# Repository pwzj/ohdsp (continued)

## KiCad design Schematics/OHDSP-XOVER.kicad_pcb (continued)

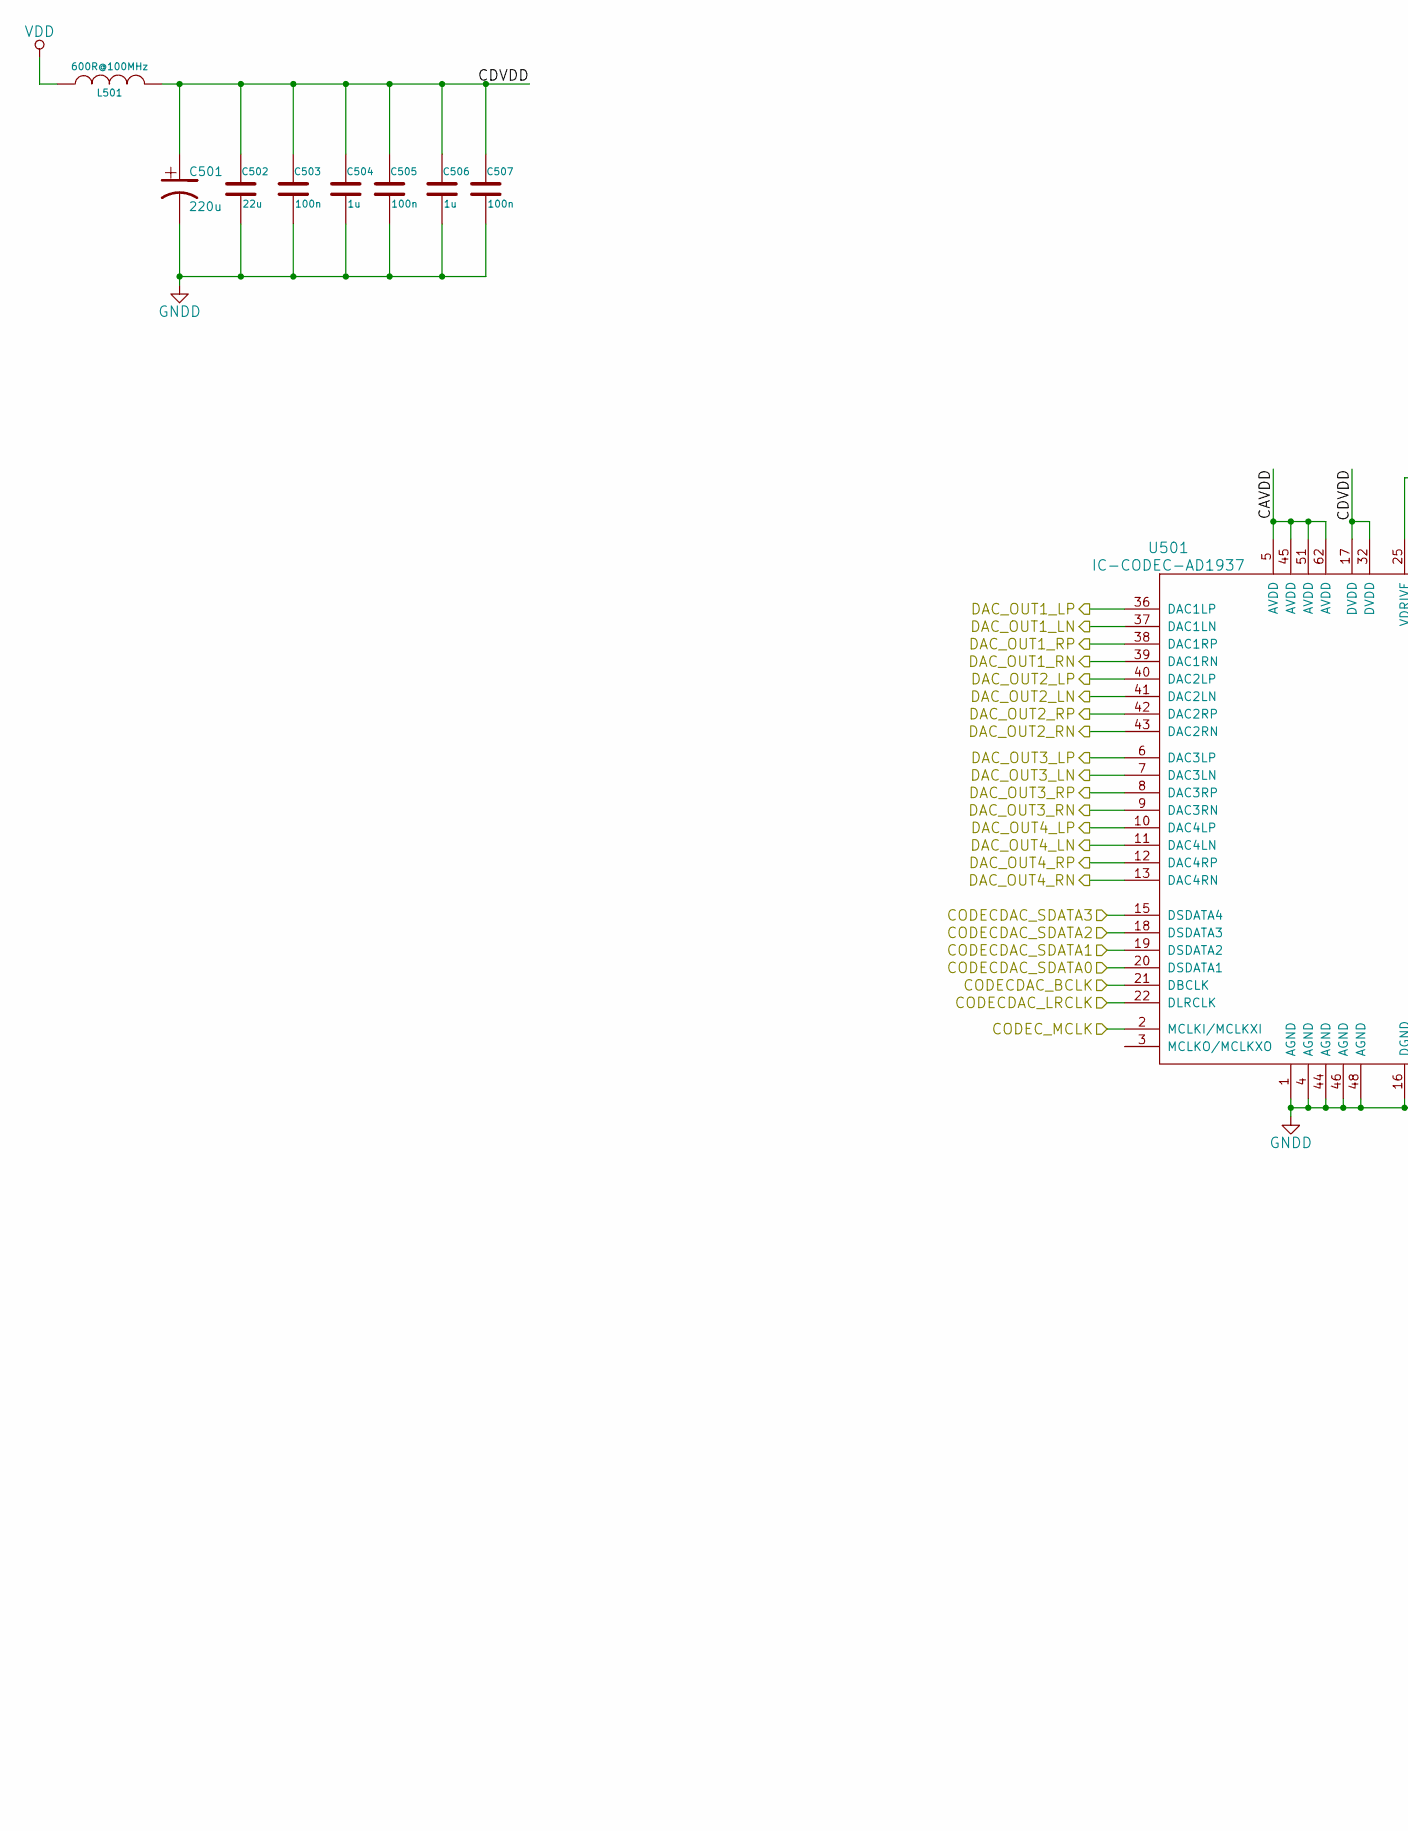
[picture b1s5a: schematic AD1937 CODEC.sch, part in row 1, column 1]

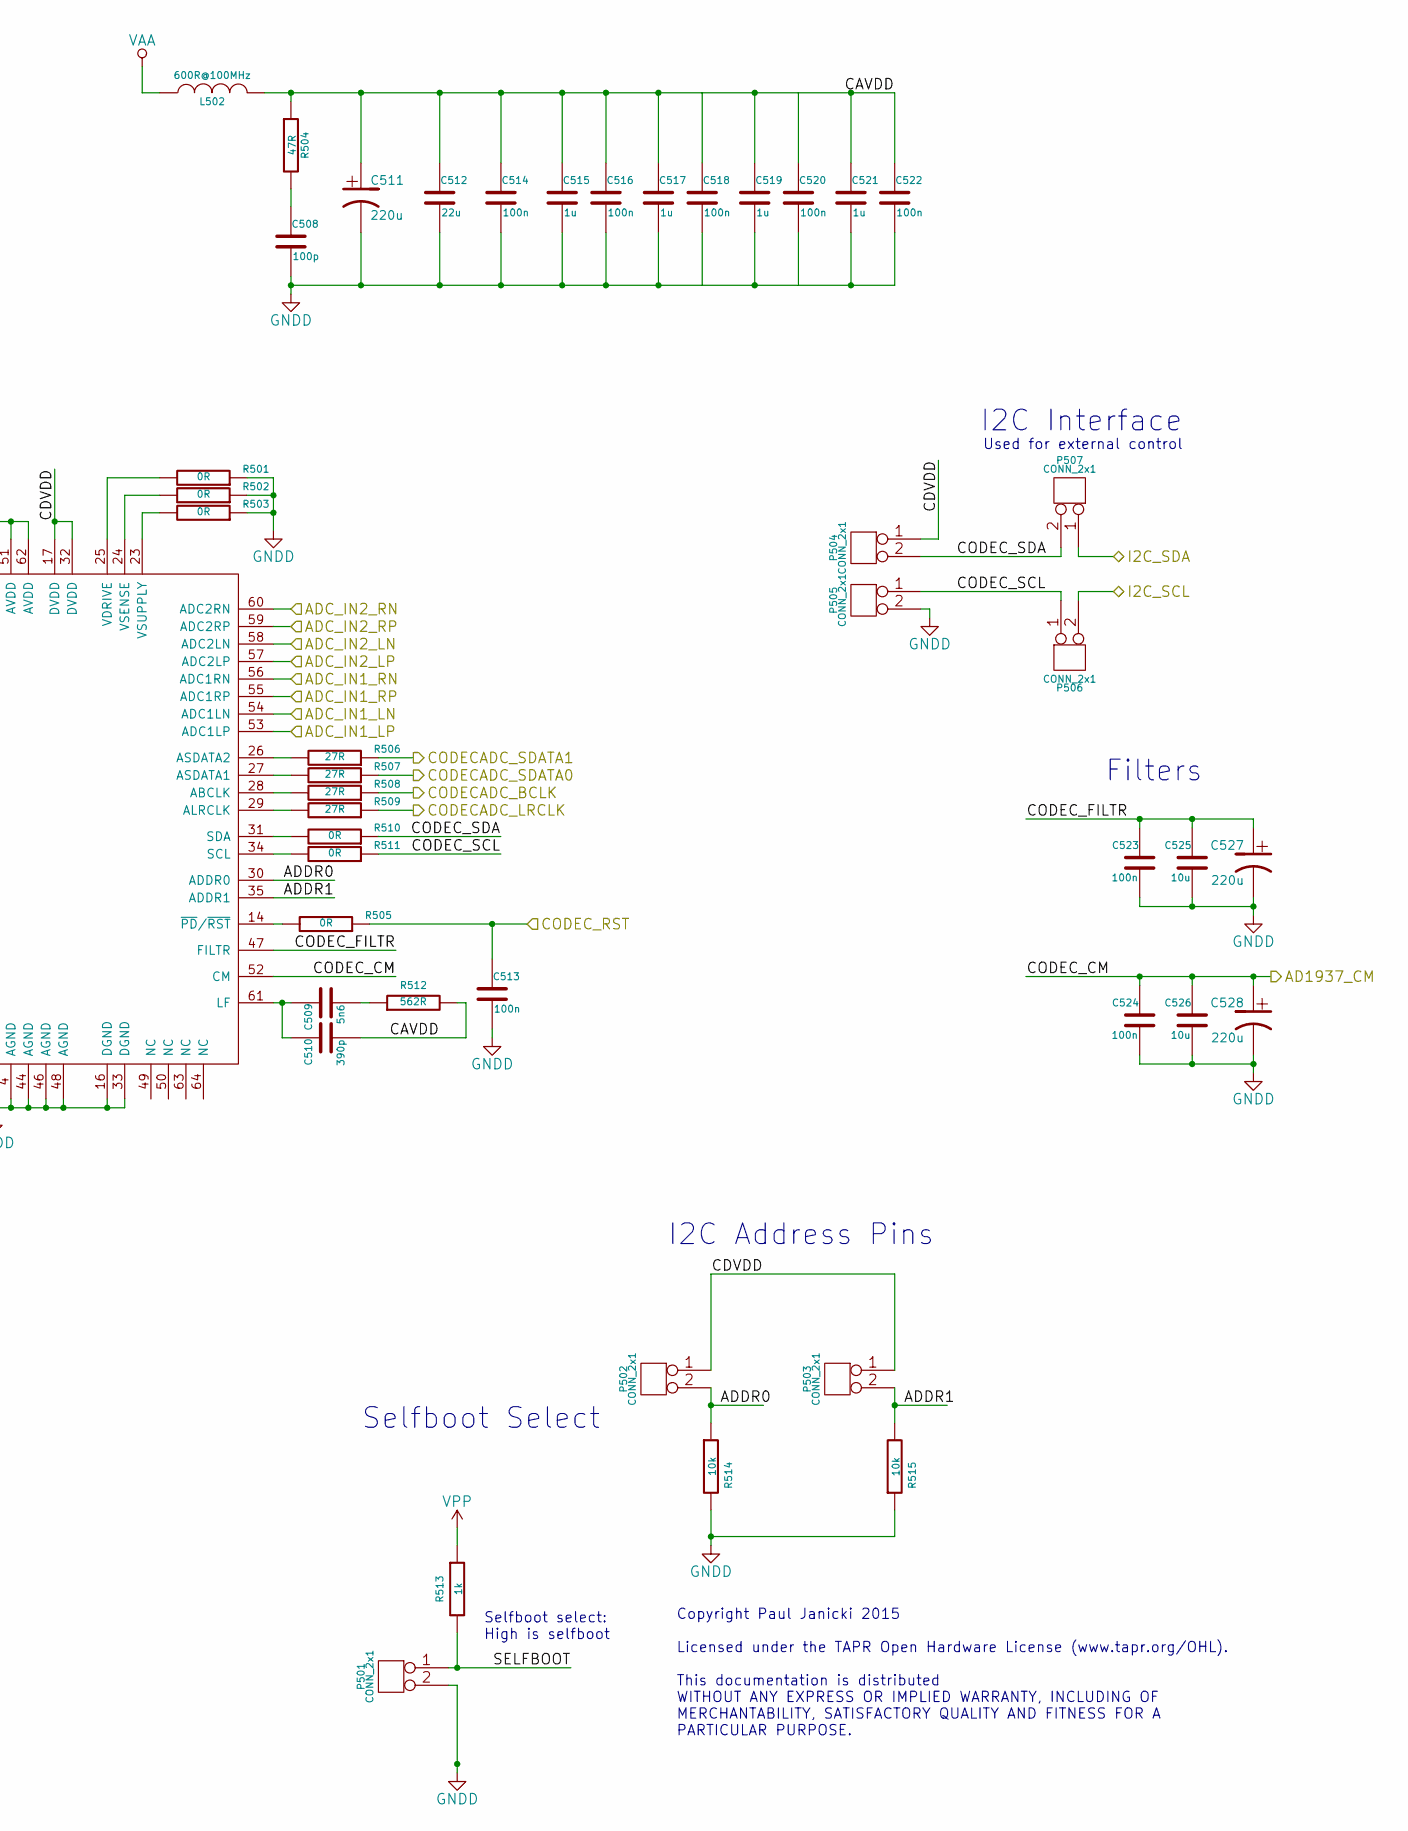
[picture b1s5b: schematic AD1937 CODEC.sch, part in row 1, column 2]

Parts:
C501, C527, C528: 220u; CAP-TH-D6.3mmP2.5mm
C502, C512: 22u; SMD-0805
C503, C505, C507, C513, C514, C516, C518, C520, C522, C523, C524: 100n; SMD-0805
C504, C506, C515, C517, C519, C521: 1u; SMD-0805
C508: 100p; SMD-0805
C509: 5n6; SMD-0805
C510: 390p; SMD-0805
C511: 220u; CAP-TH-D8mmP3.5mm
C525, C526: 10u; SMD-0805
L501, L502: 600R@100MHz; SMD-0805
P501, P502, P503, P504, P505, P506, P507: CONN_2x1; CONN_SIL_2
R501, R502, R503, R505, R510, R511: 0R; SMD-0805
R504: 47R; SMD-0805
R506, R507, R508, R509: 27R; SMD-0805
R512: 562R; SMD-0805
R513: 1k; SMD-0805
R514, R515: 10k; SMD-0805
U501: IC-CODEC-AD1937; IC-LQFP64

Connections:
/AD1937 CODEC/AD1937_CM: C524.1, C526.1, C528.1, U501.52 (CM); also elsewhere on the board
/AD1937 CODEC/ADDR0: P502.2, R514.1, U501.30 (ADDR0)
/AD1937 CODEC/ADDR1: P503.2, R515.2, U501.35 (ADDR1)
/AD1937 CODEC/CAVDD: C510.2, C511.1, C512.1, C514.1, C515.1, C516.1, C517.1, C519.1, C521.1, C522.1, L502.2, R504.1, R512.2, U501.5 (AVDD), U501.45 (AVDD), U501.51 (AVDD), U501.62 (AVDD)
/AD1937 CODEC/CDVDD: C501.1, C502.1, C503.1, C504.1, C505.1, C506.1, C507.1, L501.2, P502.1, P503.1, P504.1, U501.17 (DVDD), U501.32 (DVDD)
/AD1937 CODEC/CODECDAC_BCLK: U501.21 (DBCLK); also elsewhere on the board
/AD1937 CODEC/CODECDAC_LRCLK: U501.22 (DLRCLK); also elsewhere on the board
/AD1937 CODEC/CODECDAC_SDATA0: U501.20 (DSDATA1); also elsewhere on the board
/AD1937 CODEC/CODECDAC_SDATA1: U501.19 (DSDATA2); also elsewhere on the board
/AD1937 CODEC/CODECDAC_SDATA2: U501.18 (DSDATA3); also elsewhere on the board
/AD1937 CODEC/CODECDAC_SDATA3: U501.15 (DSDATA4); also elsewhere on the board
/AD1937 CODEC/CODEC_FILTR: C523.1, C525.1, C527.1, U501.47 (FILTR)
/AD1937 CODEC/CODEC_MCLK: U501.2 (MCLKI/MCLKXI); also elsewhere on the board
/AD1937 CODEC/CODEC_RST: C513.1, R505.1; also elsewhere on the board
/AD1937 CODEC/CODEC_SCL: P505.1, P506.1, R511.1
/AD1937 CODEC/CODEC_SDA: P504.2, P507.2, R510.1
/AD1937 CODEC/DAC_OUT1_LN: U501.37 (DAC1LN); also elsewhere on the board
/AD1937 CODEC/DAC_OUT1_LP: U501.36 (DAC1LP); also elsewhere on the board
/AD1937 CODEC/DAC_OUT1_RN: U501.39 (DAC1RN); also elsewhere on the board
/AD1937 CODEC/DAC_OUT1_RP: U501.38 (DAC1RP); also elsewhere on the board
/AD1937 CODEC/DAC_OUT2_LN: U501.41 (DAC2LN); also elsewhere on the board
/AD1937 CODEC/DAC_OUT2_LP: U501.40 (DAC2LP); also elsewhere on the board
/AD1937 CODEC/DAC_OUT2_RN: U501.43 (DAC2RN); also elsewhere on the board
/AD1937 CODEC/DAC_OUT2_RP: U501.42 (DAC2RP); also elsewhere on the board
/AD1937 CODEC/DAC_OUT3_LN: U501.7 (DAC3LN); also elsewhere on the board
/AD1937 CODEC/DAC_OUT3_LP: U501.6 (DAC3LP); also elsewhere on the board
/AD1937 CODEC/DAC_OUT3_RN: U501.9 (DAC3RN); also elsewhere on the board
/AD1937 CODEC/DAC_OUT3_RP: U501.8 (DAC3RP); also elsewhere on the board
/AD1937 CODEC/DAC_OUT4_LN: U501.11 (DAC4LN); also elsewhere on the board
/AD1937 CODEC/DAC_OUT4_LP: U501.10 (DAC4LP); also elsewhere on the board
/AD1937 CODEC/DAC_OUT4_RN: U501.13 (DAC4RN); also elsewhere on the board
/AD1937 CODEC/DAC_OUT4_RP: U501.12 (DAC4RP); also elsewhere on the board
/AD1937 CODEC/I2C_SCL: P506.2; also elsewhere on the board
/AD1937 CODEC/I2C_SDA: P507.1; also elsewhere on the board
/AD1937 CODEC/SELFBOOT: P501.1, R513.2
/AD1937_AnaIn/AD1937_ANAIN_1N: U501.54 (ADC1LN); also elsewhere on the board
/AD1937_AnaIn/AD1937_ANAIN_1P: U501.53 (ADC1LP); also elsewhere on the board
/AD1937_AnaIn/AD1937_ANAIN_2N: U501.56 (ADC1RN); also elsewhere on the board
/AD1937_AnaIn/AD1937_ANAIN_2P: U501.55 (ADC1RP); also elsewhere on the board
/AD1937_AnaIn/AD1937_ANAIN_3N: U501.58 (ADC2LN); also elsewhere on the board
/AD1937_AnaIn/AD1937_ANAIN_3P: U501.57 (ADC2LP); also elsewhere on the board
/AD1937_AnaIn/AD1937_ANAIN_4N: U501.60 (ADC2RN); also elsewhere on the board
/AD1937_AnaIn/AD1937_ANAIN_4P: U501.59 (ADC2RP); also elsewhere on the board
/ADAU1701/ADCIN_BCLK0: R508.1; also elsewhere on the board
/ADAU1701/ADCIN_LRCLK0: R509.1; also elsewhere on the board
/ADAU1701/ADCIN_SDATA0: R507.1; also elsewhere on the board
/ADAU1701/ADCIN_SDATA1: R506.1; also elsewhere on the board
GNDD: C501.2, C502.2, C503.2, C504.2, C505.2, C506.2, C507.2, C508.2, C511.2, C512.2, C513.2, C514.2, C515.2, C516.2, C517.2, C519.2, C521.2, C522.2, C523.2, C524.2, C525.2, C526.2, C527.2, C528.2, P501.2, P505.2, R501.1, R502.1, R503.1, R514.2, R515.1, U501.1 (AGND), U501.4 (AGND), U501.16 (DGND), U501.33 (DGND), U501.44 (AGND), U501.46 (AGND), U501.48 (AGND); also elsewhere on the board
unnamed: C508.1, R504.2
unnamed: C509.1, C510.1, U501.61 (LF)
unnamed: C509.2, R512.1
unnamed: R501.2, U501.25 (VDRIVE)
unnamed: R502.2, U501.24 (VSENSE)
unnamed: R503.2, U501.23 (VSUPPLY)
unnamed: R505.2, U501.14 (~PD~/~RST)
unnamed: R506.2, U501.26 (ASDATA2)
unnamed: R507.2, U501.27 (ASDATA1)
unnamed: R508.2, U501.28 (ABCLK)
unnamed: R509.2, U501.29 (ALRCLK)
unnamed: R510.2, U501.31 (SDA)
unnamed: R511.2, U501.34 (SCL)
VAA: L502.1; also elsewhere on the board
VDD: L501.1; also elsewhere on the board
VPP: R513.1; also elsewhere on the board

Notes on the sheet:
Selfboot Select
Selfboot select: High is selfboot
I2C Interface
Used for external control
Copyright Paul Janicki 2015 Licensed under the TAPR Open Hardware License (www.tapr.org/OHL). This documentation is distributed WITHOUT ANY EXPRESS OR IMPLIED WARRANTY, INCLUDING OF MERCHANTABILITY, SATISFACTORY QUALITY AND FITNESS FOR A PARTICULAR PURPOSE.
I2C Address Pins
Filters

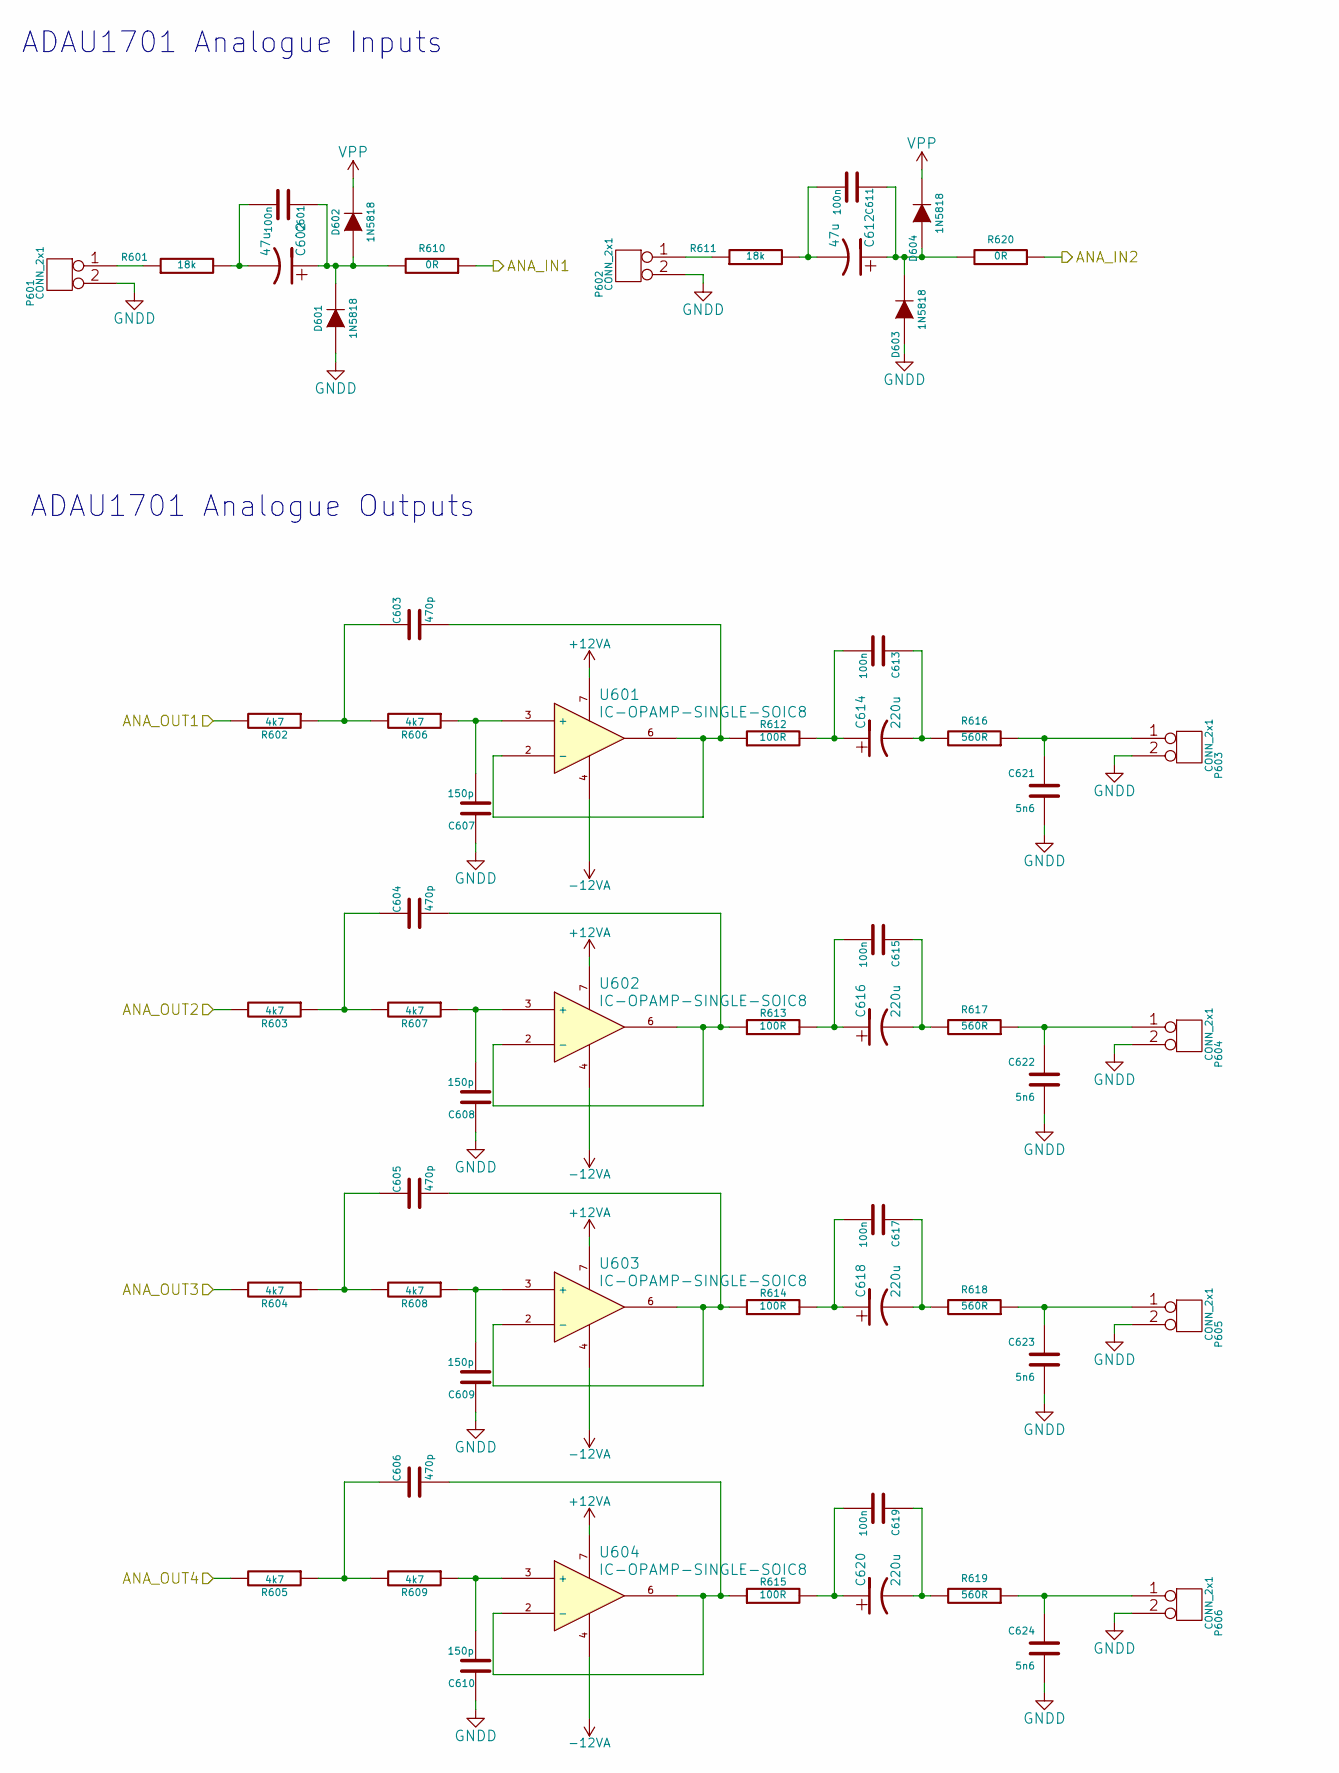
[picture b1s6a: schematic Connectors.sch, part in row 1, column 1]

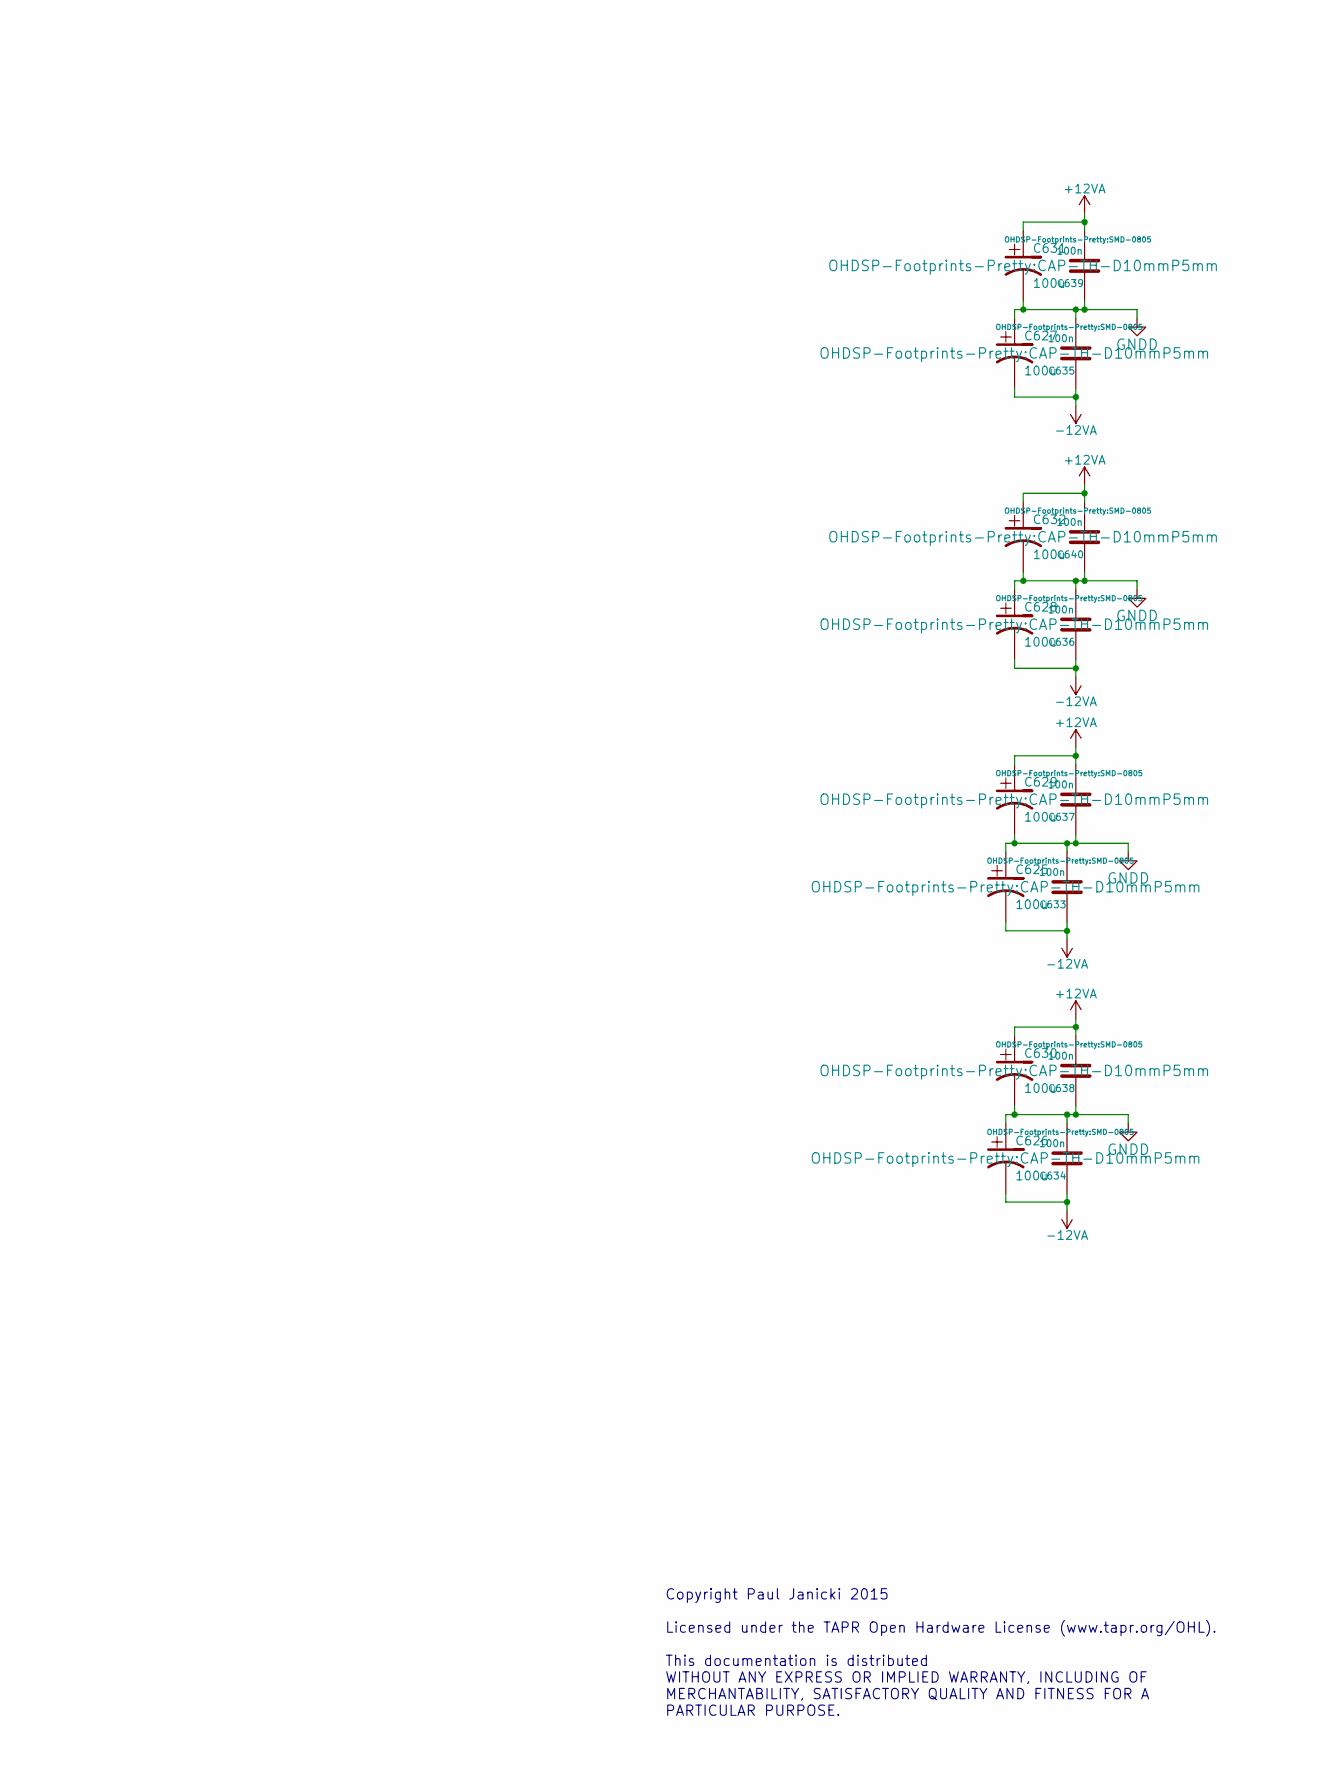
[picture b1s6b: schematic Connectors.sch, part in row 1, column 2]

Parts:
C601, C611, C613, C615, C617, C619: 100n; CAP_TH_5mm
C602, C612: 47u; CAP-TH-D10mmP5mm
C603, C604, C605, C606: 470p; CAP_TH_5mm
C607, C608, C609, C610: 150p; CAP_TH_5mm
C614, C616, C618, C620: 220u; CAP-TH-D10mmP5mm
C621, C622, C623, C624: 5n6; CAP_TH_5mm
C625, C626, C627, C628, C629, C630, C631, C632: 100u; CAP-TH-D10mmP5mm
C633, C634, C635, C636, C637, C638, C639, C640: 100n; SMD-0805
D601, D602, D603, D604: 1N5818; DIODE-DO-41
P601, P602, P603, P604, P605, P606: CONN_2x1; CONN_SIL_2
R601, R611: 18k; TH-RES-0W25
R602, R603, R604, R605, R606, R607, R608, R609: 4k7; TH-RES-0W25
R610, R620: 0R; TH-RES-0W25
R612, R613, R614, R615: 100R; TH-RES-0W25
R616, R617, R618, R619: 560R; TH-RES-0W25
U601, U602, U603, U604: IC-OPAMP-SINGLE-SOIC8; IC_DIP_8

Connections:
+12VA: C629.1, C630.1, C631.1, C632.1, C637.2, C638.2, C639.2, C640.2, U601.7, U602.7, U603.7, U604.7; also elsewhere on the board
-12VA: C625.2, C626.2, C627.2, C628.2, C633.1, C634.1, C635.1, C636.1, U601.4, U602.4, U603.4, U604.4; also elsewhere on the board
/ADAU1701/ADC_IN0: R610.1; also elsewhere on the board
/ADAU1701/ADC_IN1: R620.1; also elsewhere on the board
/Connectors/ANA_OUT1: R602.2; also elsewhere on the board
/Connectors/ANA_OUT2: R603.2; also elsewhere on the board
/Connectors/ANA_OUT3: R604.2; also elsewhere on the board
/Connectors/ANA_OUT4: R605.2; also elsewhere on the board
GNDD: C607.1, C608.1, C609.1, C610.1, C621.2, C622.2, C623.2, C624.2, C625.1, C626.1, C627.1, C628.1, C629.2, C630.2, C631.2, C632.2, C633.2, C634.2, C635.2, C636.2, C637.1, C638.1, C639.1, C640.1, D601.1 (A), D603.1 (A), P601.2, P602.2, P603.2, P604.2, P605.2, P606.2; also elsewhere on the board
unnamed: C601.1, C602.1, D601.2 (K), D602.1 (A), R610.2
unnamed: C601.2, C602.2, R601.2
unnamed: C603.1, R602.1, R606.2
unnamed: C603.2, R612.1, U601.2 (-), U601.6
unnamed: C604.1, R603.1, R607.2
unnamed: C604.2, R613.1, U602.2 (-), U602.6
unnamed: C605.1, R604.1, R608.2
unnamed: C605.2, R614.1, U603.2 (-), U603.6
unnamed: C606.1, R605.1, R609.2
unnamed: C606.2, R615.1, U604.2 (-), U604.6
unnamed: C607.2, R606.1, U601.3 (+)
unnamed: C608.2, R607.1, U602.3 (+)
unnamed: C609.2, R608.1, U603.3 (+)
unnamed: C610.2, R609.1, U604.3 (+)
unnamed: C611.1, C612.1, D603.2 (K), D604.1 (A), R620.2
unnamed: C611.2, C612.2, R611.2
unnamed: C613.1, C614.2, R616.2
unnamed: C613.2, C614.1, R612.2
unnamed: C615.1, C616.2, R617.2
unnamed: C615.2, C616.1, R613.2
unnamed: C617.1, C618.2, R618.2
unnamed: C617.2, C618.1, R614.2
unnamed: C619.1, C620.2, R619.2
unnamed: C619.2, C620.1, R615.2
unnamed: C621.1, P603.1, R616.1
unnamed: C622.1, P604.1, R617.1
unnamed: C623.1, P605.1, R618.1
unnamed: C624.1, P606.1, R619.1
unnamed: P601.1, R601.1
unnamed: P602.1, R611.1
VPP: D602.2 (K), D604.2 (K); also elsewhere on the board

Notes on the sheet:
ADAU1701 Analogue Inputs
Copyright Paul Janicki 2015 Licensed under the TAPR Open Hardware License (www.tapr.org/OHL). This documentation is distributed WITHOUT ANY EXPRESS OR IMPLIED WARRANTY, INCLUDING OF MERCHANTABILITY, SATISFACTORY QUALITY AND FITNESS FOR A PARTICULAR PURPOSE.
ADAU1701 Analogue Outputs
